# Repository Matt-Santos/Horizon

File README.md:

# Horizon (Planning Stage)

## Project Description
A high precision experimental bicopter with customized control system. 
 
## Research Hypothisis
A bicopter design when implemented using an unstable thrust to center of mass point can perform with equivalent mobility to that of the simlified quadcopter version through the use of an advanced control system. 

## Evaluation Criteria
To test this theory I purposely design an unstable thrust/weight configuration to enhance reactibility/mobility of the traditional bicopter configuration to avoid the added requirement of pitch control and improve overall efficiency.

## Todo List
- [ ] Perform Literature Review
- [ ] Identify Key Varriables
- [ ] Create Mathematical Model
- [ ] Perform Model Simulations
- [ ] Fabricate a Design Prototype
- [ ] Perform Experiemental Evaluation
- [ ] Create Publication of Findings

## Potential Usage Applications
- Atmospheric Monitoring
- Camera Mapping
- Antenna Testing

## Hardware Components
- [EMAX MT2213 935KV](https://emaxmodel.com/products/emax-mt2213-935kv-multicopter-brushless-motor) Multicopter Brushless Motor
- EMAX1045 Propeller
- [EMAX Simon Series 20A](https://emaxmodel.com/products/emax-simon-series-20a-for-muti-copter)

## Extra Notes

### Transport Canadian Drone Requirements

Note: Can avoid the AOL if takeoff weight is < 250g (goal)

Advanced Operations Licence (AOL)
- [ ] Advanced Drone Pilot Certificate
	- Pass Small Advanced Exam
	- Pass Flight Review
- [ ] Registered and Marked Drone
- [ ] RPAS Flight Authorization (for Controlled Airspace)
- [ ] RPAS Safety Declaration
	- Conforms to [Advisory Circular (AC) No. 922-001](https://tc.canada.ca/en/aviation/reference-centre/advisory-circulars/advisory-circular-ac-no-922-001)

Flight Restrictions (with AOL)
- Max Height AGL = 122m
- Operations in controlled and uncontrolled airspace
- Operations near people: less than 30 meters (100 feet) but more than 5 meters (16.4 feet) horizontally
- Operations over people: less than 5 meters (16.4 feet) horizontally
- Operations less than 3 nautical miles from a certified airport or a military aerodrome
- Operations less than 1 nautical mile from a certified heliport

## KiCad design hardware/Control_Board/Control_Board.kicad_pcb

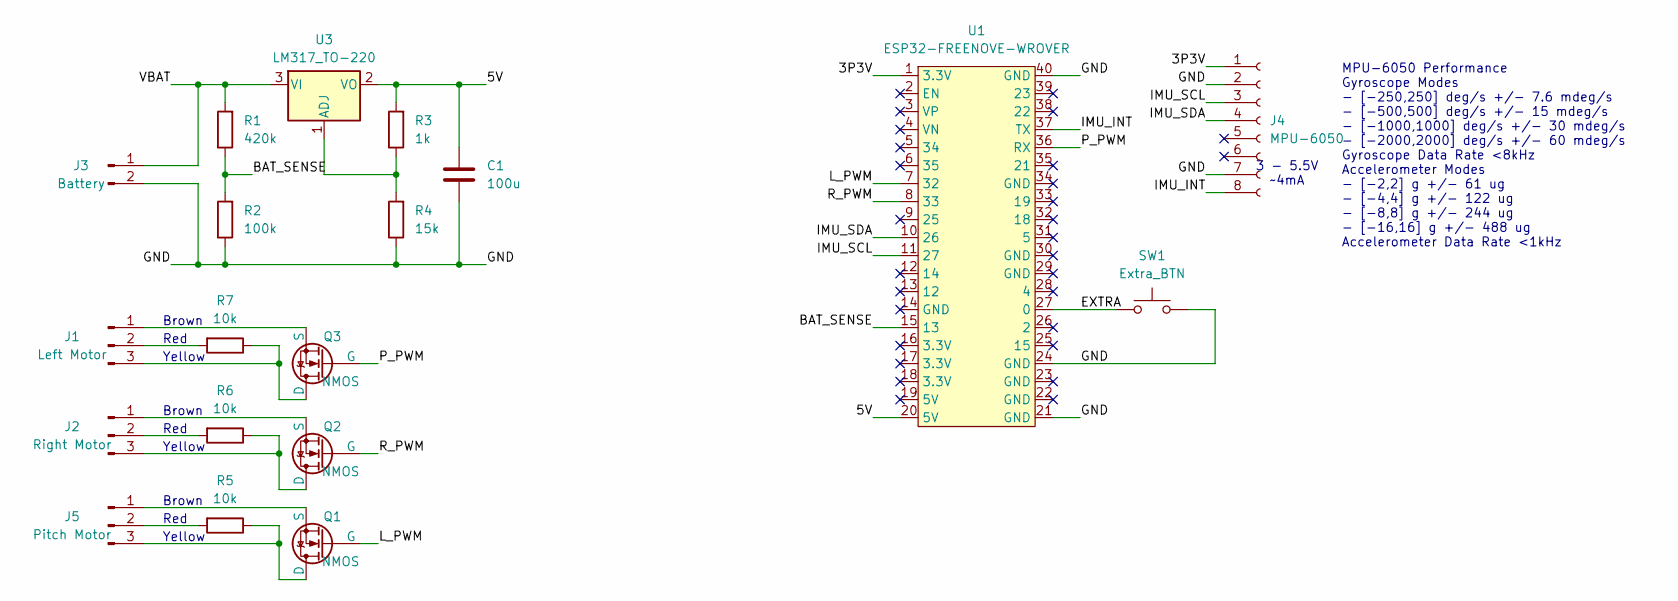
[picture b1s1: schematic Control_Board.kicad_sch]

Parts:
C1: 100u; C_Disc_D3.0mm_W1.6mm_P2.50mm
J1: Left Motor; PinHeader_1x03_P2.54mm_Vertical
J2: Right Motor; PinHeader_1x03_P2.54mm_Vertical
J3: Battery; PinHeader_1x02_P2.54mm_Vertical
J4: MPU-6050; PinSocket_1x08_P2.54mm_Vertical
J5: Pitch Motor; PinHeader_1x03_P2.54mm_Vertical
Q1, Q2, Q3: NMOS; PinHeader_1x03_P2.54mm_Vertical
R1: 420k; R_Axial_DIN0207_L6.3mm_D2.5mm_P10.16mm_Horizontal
R2: 100k; R_Axial_DIN0207_L6.3mm_D2.5mm_P10.16mm_Horizontal
R3: 1k; R_Axial_DIN0207_L6.3mm_D2.5mm_P10.16mm_Horizontal
R4: 15k; R_Axial_DIN0207_L6.3mm_D2.5mm_P10.16mm_Horizontal
R5, R6, R7: 10k; R_Axial_DIN0207_L6.3mm_D2.5mm_P10.16mm_Horizontal
SW1: Extra_BTN
U1: ESP32-FREENOVE-WROVER
U3: LM317_TO-220; TO-220-3_Vertical

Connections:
/3P3V: J4.1, U1.1 (3.3V)
/5V: C1.1, R3.2, U1.20 (5V), U3.2 (VO)
/BAT_SENSE: R1.1, R2.2, U1.15 (13)
/EXTRA: SW1.1, U1.27 (0)
/GND: C1.2, J3.2, J4.2, J4.7, R2.1, R4.1, SW1.2, U1.21 (GND), U1.24 (GND), U1.40 (GND)
/IMU_INT: J4.8, U1.37 (TX)
/IMU_SCL: J4.3, U1.11 (27)
/IMU_SDA: J4.4, U1.10 (26)
/L_PWM: Q1.2 (G), U1.7 (32)
/P_PWM: Q3.2 (G), U1.36 (RX)
/R_PWM: Q2.2 (G), U1.8 (33)
/VBAT: J3.1, R1.2, U3.3 (VI)
unnamed: J1.1, Q3.3 (S)
unnamed: J1.2, R7.2
unnamed: J1.3, Q3.1 (D), R7.1
unnamed: J2.1, Q2.3 (S)
unnamed: J2.2, R6.2
unnamed: J2.3, Q2.1 (D), R6.1
unnamed: J5.1, Q1.3 (S)
unnamed: J5.2, R5.2
unnamed: J5.3, Q1.1 (D), R5.1
unnamed: R3.1, R4.2, U3.1 (ADJ)

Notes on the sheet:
Brown
MPU-6050 Performance Gyroscope Modes - [-250,250] deg/s +/- 7.6 mdeg/s - [-500,500] deg/s +/- 15 mdeg/s - [-1000,1000] deg/s +/- 30 mdeg/s - [-2000,2000] deg/s +/- 60 mdeg/s Gyroscope Data Rate <8kHz Accelerometer Modes - [-2,2] g +/- 61 ug - [-4,4] g +/- 122 ug - [-8,8] g +/- 244 ug - [-16,16] g +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
Red
Yellow
3 - 5.5V ~4mA

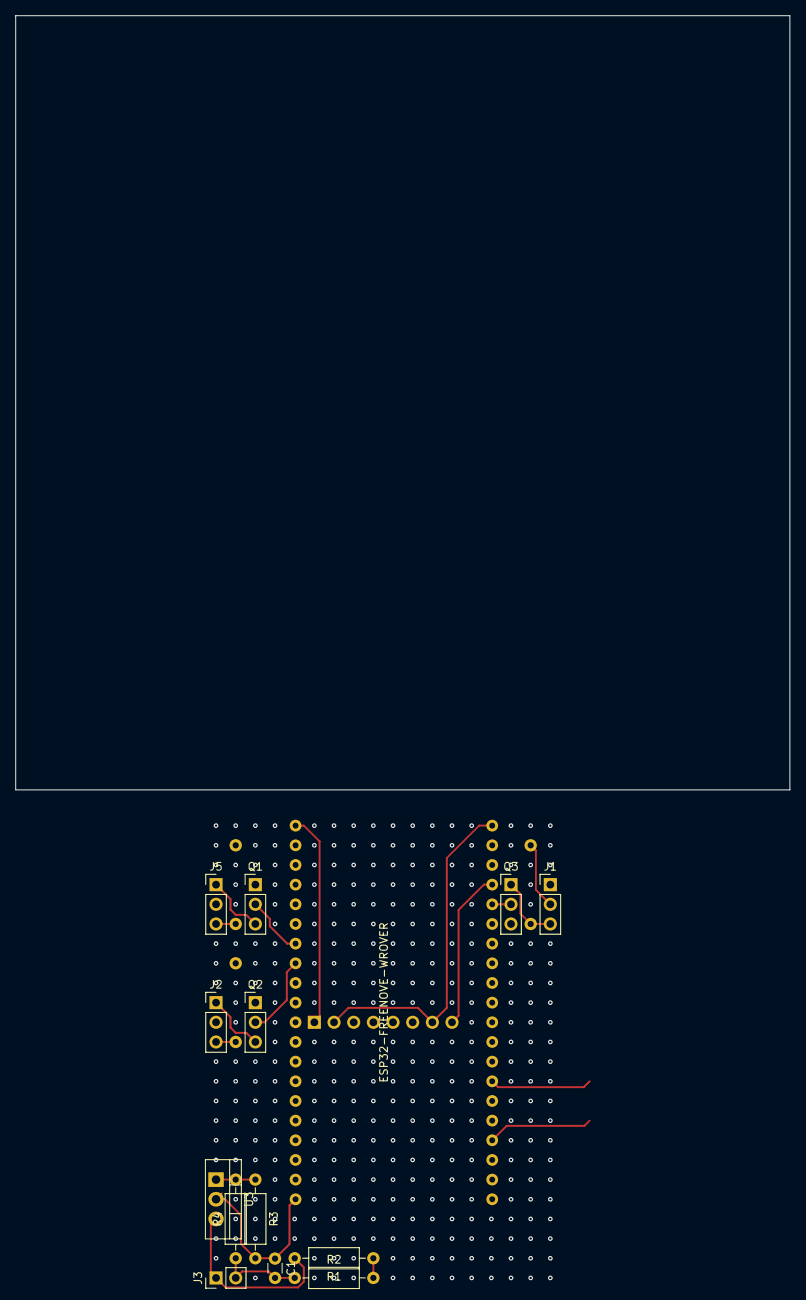
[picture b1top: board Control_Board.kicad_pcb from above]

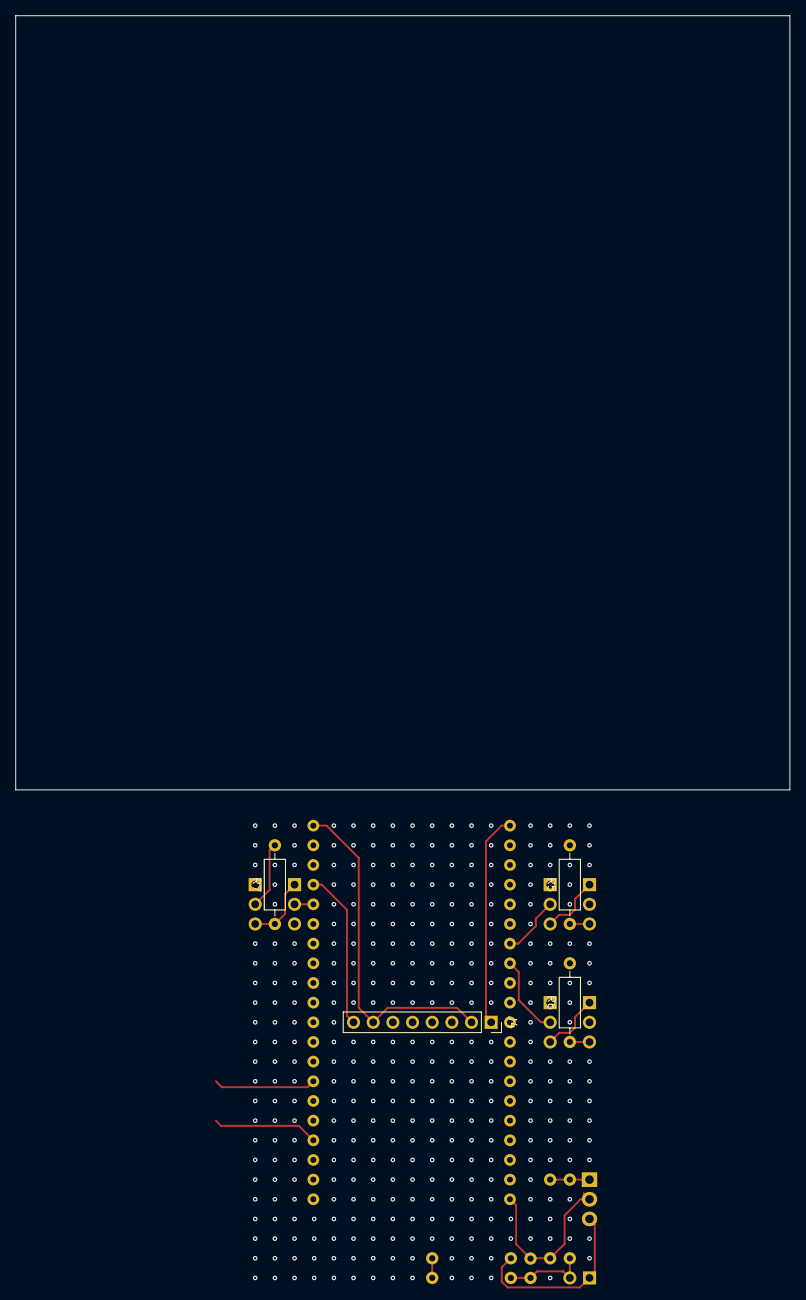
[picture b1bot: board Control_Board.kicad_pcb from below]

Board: 4 copper layers, 100.0 x 100.0 mm, 18 parts (4 on the bottom side), 21 nets.

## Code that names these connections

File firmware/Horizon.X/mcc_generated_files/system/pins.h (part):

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// get/set IO_RA2 aliases
#define BAT_SENSE_TRIS                 TRISAbits.TRISA2
#define BAT_SENSE_LAT                  LATAbits.LATA2
#define BAT_SENSE_PORT                 PORTAbits.RA2
#define BAT_SENSE_WPU                  WPUAbits.WPUA2
#define BAT_SENSE_OD                   ODCONAbits.ODA2
#define BAT_SENSE_ANS                  ANSELAbits.ANSA2
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// get/set IO_RA4 aliases
#define R_PWM_TRIS                 TRISAbits.TRISA4
#define R_PWM_LAT                  LATAbits.LATA4
#define R_PWM_PORT                 PORTAbits.RA4
#define R_PWM_WPU                  WPUAbits.WPUA4
#define R_PWM_OD                   ODCONAbits.ODA4
#define R_PWM_ANS                  ANSELAbits.ANSA4
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// get/set IO_RA5 aliases
#define L_PWM_TRIS                 TRISAbits.TRISA5
#define L_PWM_LAT                  LATAbits.LATA5
#define L_PWM_PORT                 PORTAbits.RA5
#define L_PWM_WPU                  WPUAbits.WPUA5
#define L_PWM_OD                   ODCONAbits.ODA5
#define L_PWM_ANS                  ANSELAbits.
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
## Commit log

2025-01-07 feat: add references
2025-01-13 feat: project readme + add references
2025-01-14 feat: define simulation model parameters
2025-01-15 feat: created basic control board schematic
2025-01-16 feat: create initial test board
2025-01-23 feat: update prototype with esp32
2025-01-27 feat: update and reorganize MPU Code
2025-01-28 feat: split code into class based modules
2025-01-30 fix: started code refactoring
2025-01-31 fix: save state before next refactor attempt
2025-02-01 feat: refactored code into class modules
2025-02-02 feat: added filtering to IMU sensor readings
2025-02-05 feat: completed PWM calibration procedure
2025-02-07 feat: upgraded imu code
2025-02-13 feat: update sensor system
2025-02-16 feat: added pitch servo control
2025-02-17 feat: pitch control via direct stepping
2025-02-18 feat: add timing debug and optimize
2025-02-19 feat: improve servo control
2025-02-23 fix: motor controls with new offsets
2025-03-01 feat: added experimental mpu firmware
2025-03-03 fix: moved 3rd party libraries to outside repo

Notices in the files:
firmware/Horizon.X/mcc_generated_files/system/pins.h:
© [2025] Microchip Technology Inc. and its subsidiaries.
